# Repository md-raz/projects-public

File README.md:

# projects-public
These are projects which I've worked on in the past. These projects were, or are now, made public and are no longer undisclosed. 

Each corresponding file contains information about a specific project.

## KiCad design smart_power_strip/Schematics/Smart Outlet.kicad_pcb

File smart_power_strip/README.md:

## Smart Power Strip

### About the Project:
ESP32-WROOM (XTENSA) based “smart” power strip. Device connects to WiFi network and provides a webserver interface from which connected devices can be turned on or off. Power input directly from mains (120V @ 60 Hz). Incorporates the use of solid state [opto-isolated] relays to safely toggle power on and off. Proof of concept demonstration for moderate power and current applications on silver nano-particle inkjet PCBs.

### What I Primarily Worked On:
Designed the schematic, PCB design, and then fabricated the circuit. Programmed the processor using Arduino IDE (C++). Thoroughly documented creation of the device. Assembled and built device based on developed schematics.
Further information about the build process can be found at <code> https://www.botfactory.co/blog/what-s-new-at-botfactory-1/post/creating-a-smart-outlet-121 </code> 

### Disclaimer
This project is intended to show how you can prototype with an SV2 PCB printer. It is not a product that you should use as an everyday item. It was neither designed nor tested to comply with appropriate safety standards. You are liable for any risk you take when using this design.

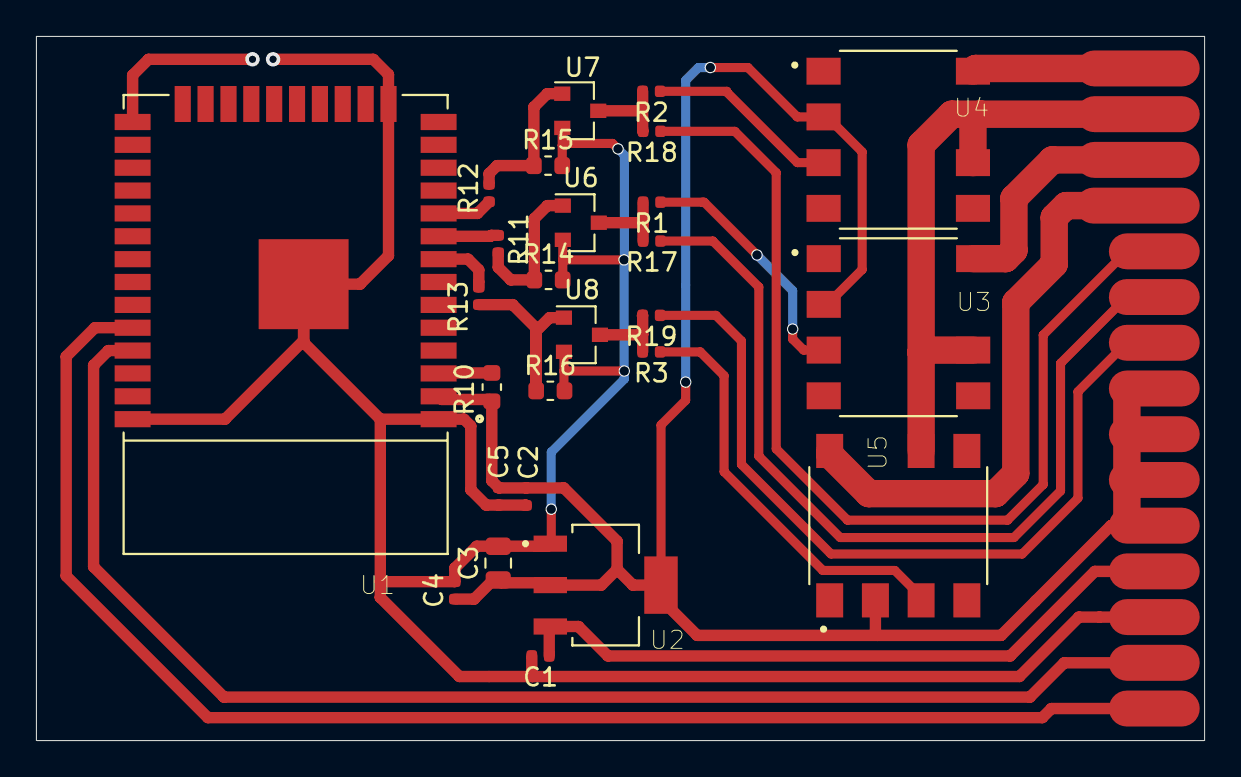
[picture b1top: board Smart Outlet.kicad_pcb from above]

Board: 2 copper layers, 64.9 x 39.1 mm, 26 parts (0 on the bottom side), 17 nets.

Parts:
C1, C2: 1uF; C_0402_1005Metric
C3: 10uF; C_0805_2012Metric
C4, C5: 0.1uF; C_0402_1005Metric
R1, R2, R3, R11, R12, R13, R17, R18, R19: 100; R_0402_1005Metric
R10, R14, R15, R16: 10k; R_0603_1608Metric
U1: ESP32-WROOM-32D; MODULE_ESP32-WROOM-32D
U2: AZ1117EH-3.3TRG1; SOT230P700X180-4N
U3, U4, U5: AH-Q; RELAY_AQH3223A
U6, U7, U8: DMN2056U; SOT-23

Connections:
+3V3: C2.1, C3.1, C4.1, C5.1, R10.2, U1.2, U2.2, U2.4, U3.2, U4.2, U5.2
+5V: C1.1, U2.3
/AC_L: U3.6, U4.6, U5.6
/Data1: R11.2, U1.9
/Data2: R12.2, U1.10
/Data3: R13.2, U1.8
GND: C1.2, C2.2, C3.2, C4.2, C5.2, R14.2, R15.2, R16.2, U1.1, U1.15, U1.38, U1.39, U2.1, U6.2, U7.2, U8.2
unnamed: R1.1, U3.3
unnamed: R1.2, R17.2, U6.3
unnamed: R2.1, U4.3
unnamed: R3.1, U5.3
unnamed: R10.1, U1.3
unnamed: R11.1, R14.1, U6.1
unnamed: R12.1, R15.1, U7.1
unnamed: R13.1, R16.1, U8.1
unnamed: R2.2, R18.2, U7.3
unnamed: R3.2, R19.2, U8.3

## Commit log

2020-12-03 Updated Files

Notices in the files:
smart_power_strip/Schematics/Smart Outlet.kicad_pcb:
(www.creativecommons.org/licenses/by-nc-sa/4.0/?ref=ccchooser)
Smart Outlet by BotFactory, Inc. (www.botfactory.co) is licensed under CC BY-NC-SA 4.0
